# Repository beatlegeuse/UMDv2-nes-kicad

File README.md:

# UMDv2-nes-kicad
UMDv2 NES Cartridge Adapter

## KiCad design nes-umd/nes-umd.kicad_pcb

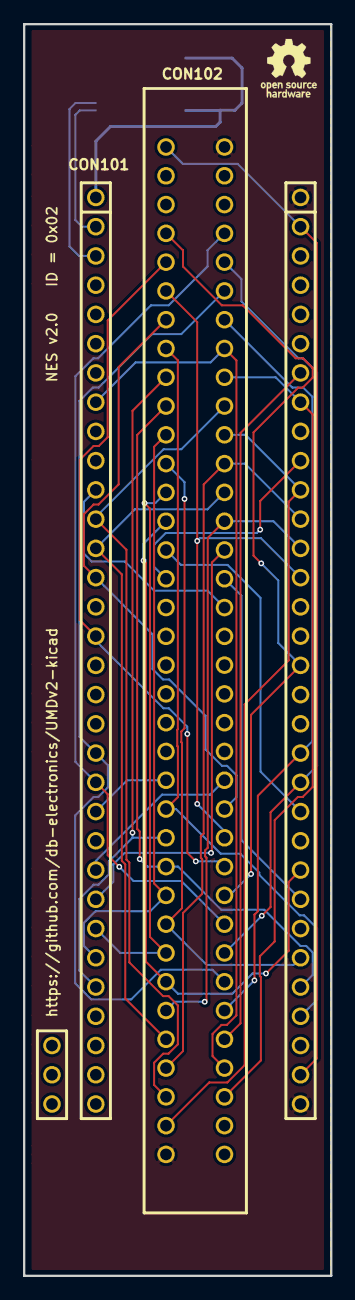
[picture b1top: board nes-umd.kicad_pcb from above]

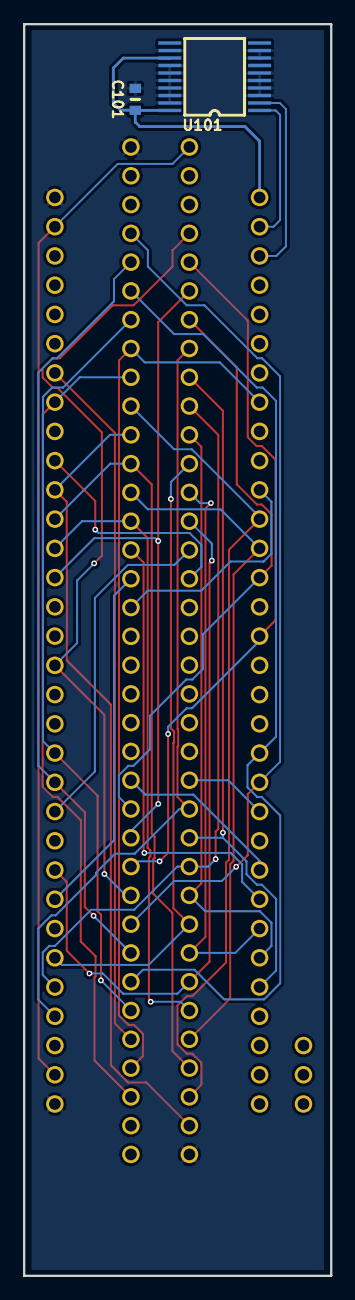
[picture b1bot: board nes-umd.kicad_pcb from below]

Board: 2 copper layers, 26.7 x 108.7 mm, 4 parts (2 on the bottom side), 35 nets.

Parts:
C101: 0.1uF/50V; 0603
CON101: UMDv2-CONN; UMD-CONN-DIP64
CON102: NES-CONN
U101: MCP23008T-E_SS; SSOP-20

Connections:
+3V3: C101.1, CON101.1, U101.13, U101.20
+5V: CON101.34, CON101.63, CON102.36
/A0: CON101.36, CON102.13, CON102.29
/A1: CON101.28, CON102.12, CON102.28
/A2: CON101.37, CON102.11, CON102.27
/A3: CON101.27, CON102.10, CON102.26
/A4: CON101.38, CON102.9, CON102.25
/A5: CON101.26, CON102.8, CON102.24
/A6: CON101.41, CON102.7, CON102.23
/A7: CON101.52, CON102.6, CON102.59
/A8: CON101.13, CON102.5, CON102.60
/A9: CON101.53, CON102.4, CON102.61
/A10: CON101.12, CON102.3, CON102.63
/A11: CON101.54, CON102.2, CON102.62
/A12: CON101.57, CON102.39, CON102.64
/A13: CON101.8, CON102.40, CON102.65
/A14: CON101.58, CON102.41
/CHR_~A13: CON101.25, CON102.58
/CHR_~RD: CON101.55, CON102.21
/CHR_~WR: CON101.11, CON102.56
/CIRAM_A10: CON101.43, CON102.22
/CIRAM_~CE: CON101.40, CON102.57
/D0: CON101.14, CON102.30, CON102.49
/D1: CON101.51, CON102.31, CON102.48
/D2: CON101.16, CON102.32, CON102.47
/D3: CON101.48, CON102.33, CON102.46
/D4: CON101.21, CON102.45, CON102.69
/D5: CON101.44, CON102.44, CON102.68
/D6: CON101.20, CON102.43, CON102.67
/D7: CON101.45, CON102.42, CON102.66
/PRG_R~W: CON101.22, CON102.14
/PRG_~CE: CON101.24, CON102.50
/SCL: CON101.2, U101.1
/SDA: CON101.3, U101.2
GND: C101.2, CON101.33, CON101.64, CON102.1, CON102.72, U101.3, U101.4, U101.5, U101.6, U101.8, U101.9, U101.12, U101.14, U101.15, U101.16, U101.17, U101.18, U101.19

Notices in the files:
nes-umd/nes-umd.kicad_pcb:
Licensed Under CERN OHL v.1.2
